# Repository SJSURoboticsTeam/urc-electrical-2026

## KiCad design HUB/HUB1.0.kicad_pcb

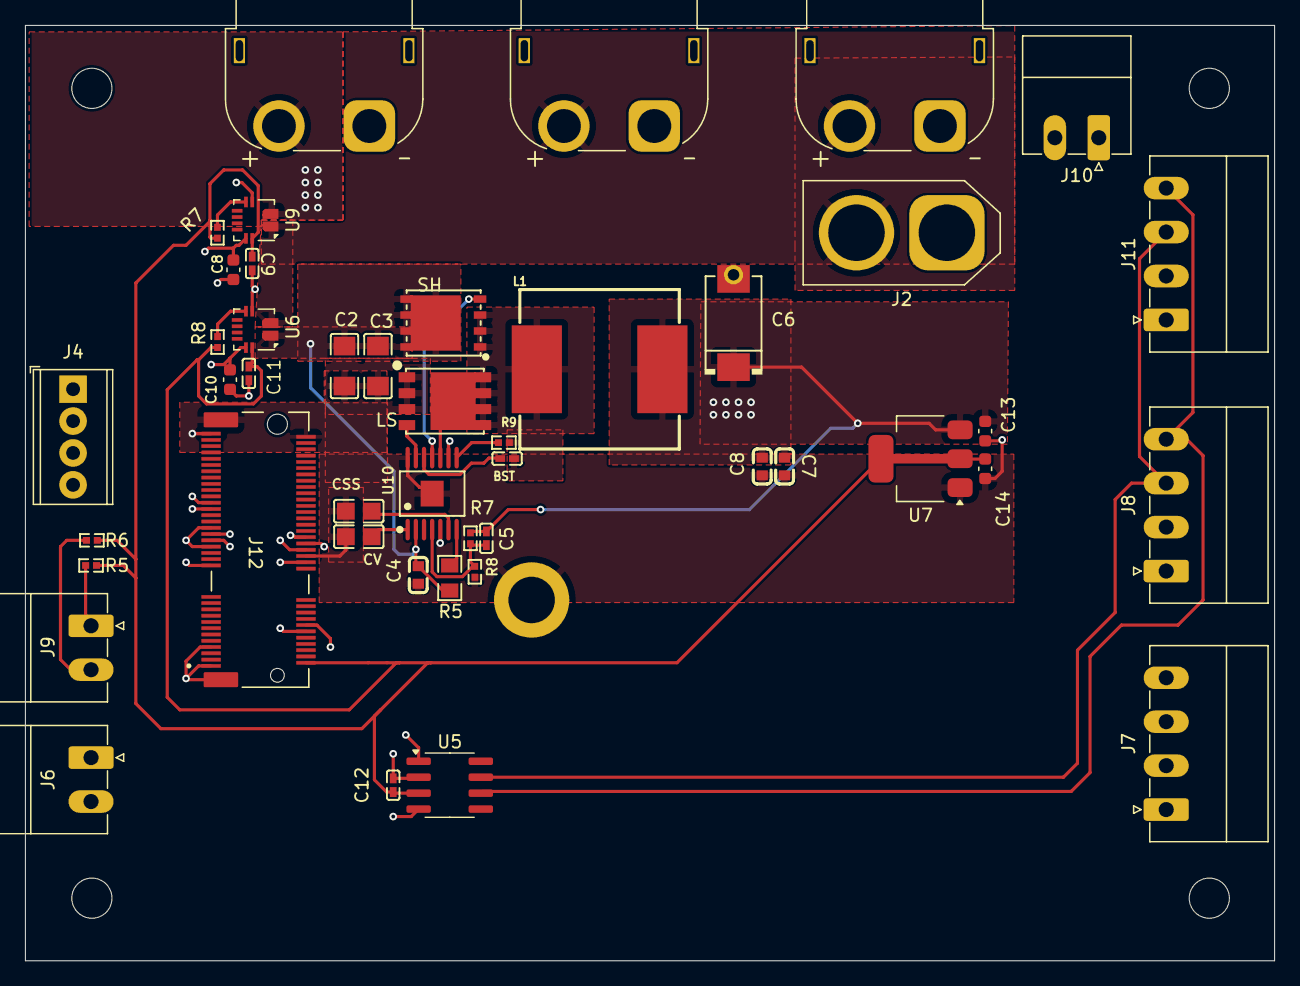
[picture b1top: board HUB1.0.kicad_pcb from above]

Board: 4 copper layers, 99.5 x 74.5 mm, 45 parts (0 on the bottom side), 29 nets.

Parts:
BST: C0402
C2, C3: C1206
C4, C7, C8#2: C0603
C5: C0402
C6: CAP-SMD_L7.3-W4.3-R-RD
C8, C10: 18pF; C_0603_1608Metric
C9, C11, C12: 100nF; C0402
C13, C14: 10µF; C_0603_1608Metric
CSS: C0805
CV: C0805
HS: DFN-8_L5.9-W5.2-P1.27-LS6.2-BL
J1, J3, J5: XT60-PW-M; AMASS_XT60PW-F_1x02_P7.20mm_Horizontal
J2: XT60-PW-M; AMASS_XT60-F_1x02_P7.20mm_Vertical
J4: 2.54mm LCD; TerminalBlock_Phoenix_MPT-0,5-4-2.54_1x04_P2.54mm_Horizontal
J6, J10: Phoenix (5V,GND); PhoenixContact_MC_1,5_2-G-3.5_1x02_P3.50mm_Horizontal
J7: Phoenix (GPIO, 5V, GND); PhoenixContact_MC_1,5_4-G-3.5_1x04_P3.50mm_Horizontal
J8, J11: Phoenix (+,-,CANH/L); PhoenixContact_MC_1,5_4-G-3.5_1x04_P3.50mm_Horizontal
J9: Phoenix (SDA/L); PhoenixContact_MC_1,5_2-G-3.5_1x02_P3.50mm_Horizontal
J12: MicroMod; micromod
L1: IND-SMD_L12.7-W12.7
LS: POWERVDFN-8_L6.0-W5.0-P1.27-BL
R5: R0805
R5#2, R6, R7, R8: 10K; R0402
R7#2, R8#2, R9: R0402
U5: SN65HVD232; SOIC-8_3.9x4.9mm_P1.27mm
U6, U9: ACS711xEXLT-31AB; Allegro_QFN-12-10-1EP_3x3mm_P0.5mm
U7: AMS1117-3.3; SOT-223-3_TabPin2
U10: HTSSOP-14_L5.0-W4.4-P0.65-LS6.4-BL-EP

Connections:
3.3V: C9.1, C11.1, C12.1, C14.1, J12.2 (VCC), R5#2.1, R6.1, R7.2, R8.2, U5.3 (VCC), U6.10 (VCC), U7.2 (VO), U9.10 (VCC)
5V: C5.1, C6.1, C7.1, C8#2.1, C13.1, J4.4, J6.1, J7.1, J8.1, J10.1, J11.1, L1.2, R7#2.2, U7.3 (VI)
40V: C2.2, C3.2, C4.2, HS.5, HS.6, HS.7, HS.8, HS.9, R5.2, U6.1 (IP+), U10.2
$2N671: BST.1, U10.12
$2N681: R5.1, U10.7
$2N1026: CSS.2, U10.6
$2N1121: CV.2, U10.1
$2N1983: C5.2, R7#2.1, R8#2.2, U10.4
$2N2778: BST.2, HS.1, HS.2, HS.3, L1.1, LS.5, LS.6, LS.7, LS.8, LS.9, R9.2, U10.10
$2N2800: LS.4, U10.13
$2N2931: R9.1, U10.8
ADC1: C8.1, J12.34 (A0), U9.9 (VIOUT)
ADC2: C10.1, J12.38 (A0), U6.9 (VIOUT)
GATE: HS.4, U10.11
GND: C2.1, C3.1, C4.1, C6.2, C7.2, C8.2, C8#2.2, C9.2, C10.2, C11.2, C12.2, C13.2, C14.2, CSS.1, CV.1, J1.1, J2.1, J3.1, J4.3, J5.1, J6.2, J7.2, J8.2, J10.2, J11.2, J12.1 (GND), J12.7 (GND), J12.33 (GND), J12.36 (GND), J12.39 (GND), J12.45 (GND), J12.74 (GND), J12.75 (GND), J12.S1 (GND), J12.S2 (GND), J12.S3 (GND), LS.1, LS.2, LS.3, R8#2.1, U5.2 (GND), U6.3 (GND), U7.1 (GND), U9.3 (GND), U10.5, U10.9, U10.14, U10.15
unnamed: J1.2, J2.2, J5.2, U6.2 (IP-), U9.1 (IP+)
unnamed: J3.2, U9.2 (IP-)
unnamed: J8.3, J11.3, U5.7 (CANH)
unnamed: J8.4, J11.4, U5.6 (CANL)
unnamed: J7.4, J12.40 (G0/BUS0)
unnamed: J7.3, J12.42 (G1/BUS1)
unnamed: R8.1, U6.4 (~FAULT)
unnamed: R7.1, U9.4 (~FAULT)
RX: J12.41 (CAN_RX), U5.4 (R)
SCL: J9.2, J12.14 (I2C_SCL), R6.2
SCL2: J4.1, J12.53 (I2C1_SCL)
SDA: J9.1, J12.12 (I2C_SDA), R5#2.2
SDA2: J4.2, J12.51 (I2C1_SDA)
TX: J12.43 (CAN_TX), U5.1 (D)

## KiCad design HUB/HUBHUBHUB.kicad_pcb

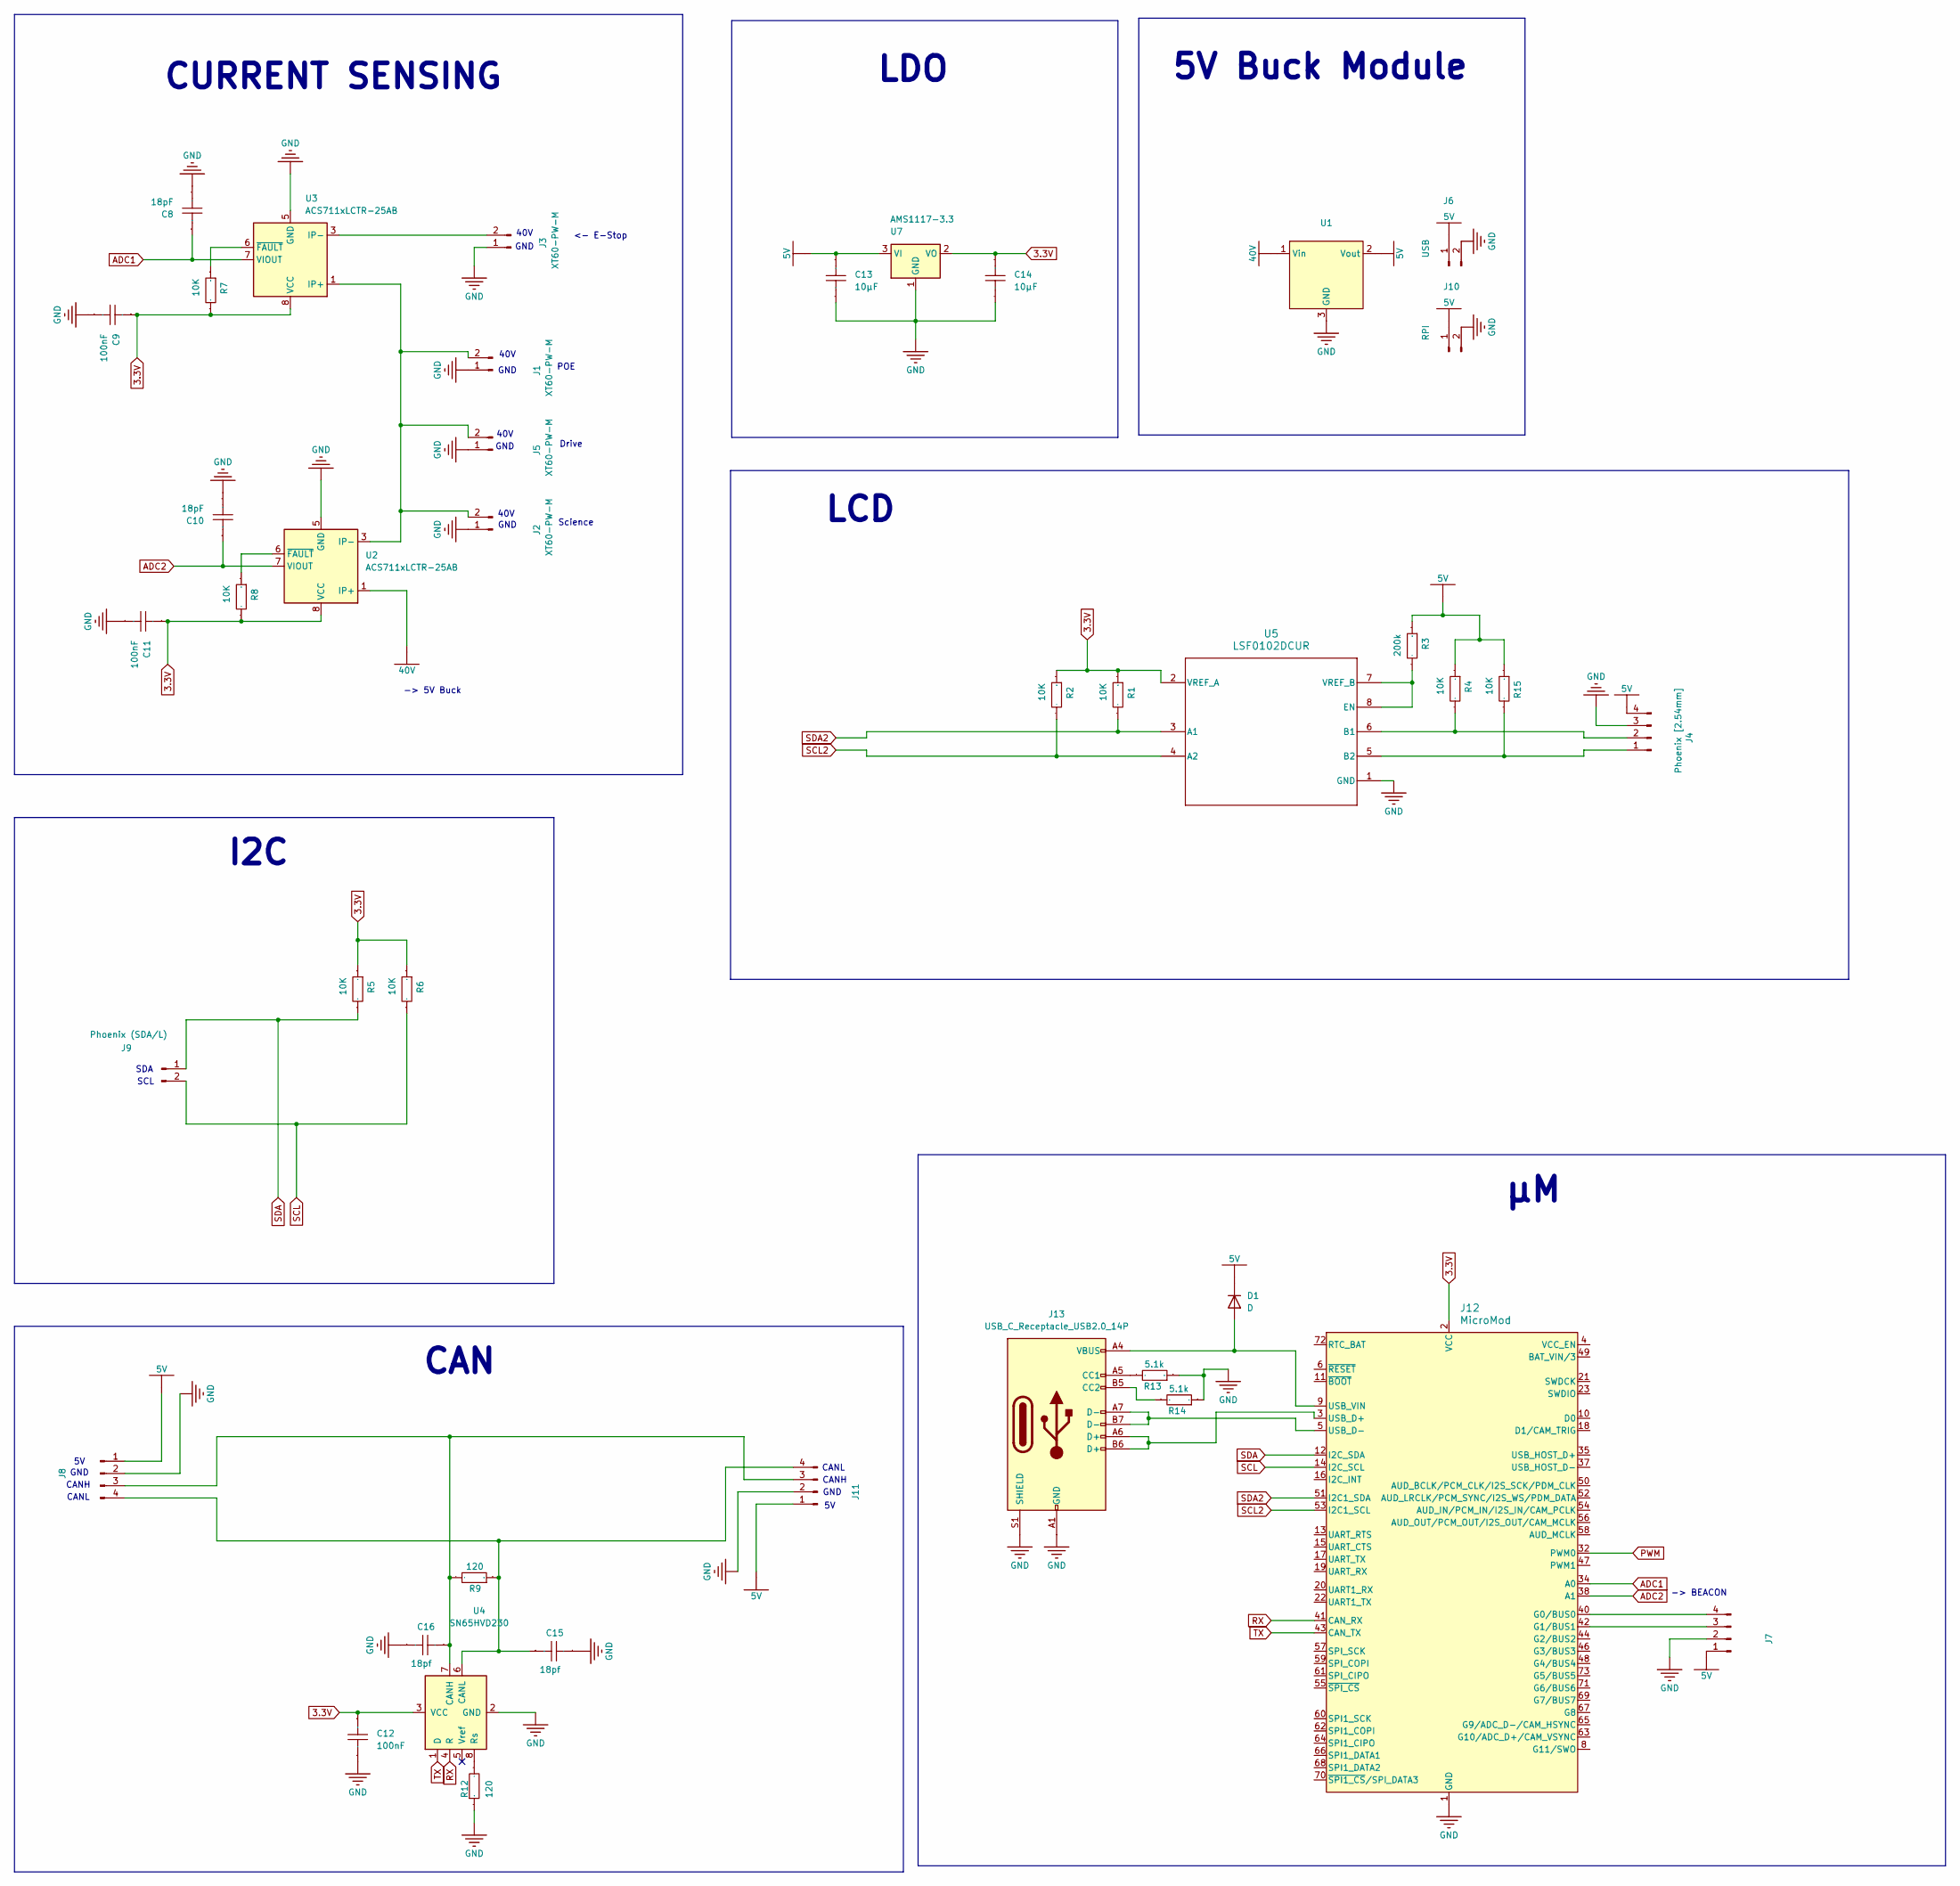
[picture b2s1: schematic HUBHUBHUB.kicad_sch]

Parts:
C8, C10: 18pF; C_0603_1608Metric
C9, C11, C12: 100nF; C0402
C13, C14: 10µF; C_0603_1608Metric
C15, C16: 18pf; C_0603_1608Metric
D1: D; Vishay_SMPA
J1, J2, J3, J5: XT60-PW-M; AMASS_XT60PW-M_1x02_P7.20mm_Horizontal
J4, J7, J8, J11: Phoenix [2.54mm]; TerminalBlock_Phoenix_MPT-0,5-4-2.54_1x04_P2.54mm_Horizontal
J6: USB; TerminalBlock_Phoenix_MPT-0,5-2-2.54_1x02_P2.54mm_Horizontal
J9: Phoenix (SDA/L); TerminalBlock_Phoenix_MPT-0,5-2-2.54_1x02_P2.54mm_Horizontal
J10: RPI; TerminalBlock_Phoenix_MPT-0,5-2-2.54_1x02_P2.54mm_Horizontal
J12: MicroMod; micromod
J13: USB_C_Receptacle_USB2.0_14P; USB_C_Receptacle_HRO_TYPE-C-31-M-12
R1, R2, R4, R5, R6, R7, R8, R15: 10K; R_0603_1608Metric
R3: 200k; R_0603_1608Metric
R9, R12: 120; R_0603_1608Metric
R13, R14: 5.1k; R_0603_1608Metric
U1: 5VBuckModule
U2, U3: ACS711xLCTR-25AB; SOIC-8_3.9x4.9mm_P1.27mm
U4: SN65HVD230; SOIC-8_3.9x4.9mm_P1.27mm
U5: LSF0102DCUR
U7: AMS1117-3.3; SOT-223-3_TabPin2

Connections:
3.3V: C9.1, C11.1, C12.1, C14.1, J12.2 (VCC), J12.74 (VCC), R1.1, R2.1, R5.1, R6.1, R7.2, R8.2, U2.8 (VCC), U3.8 (VCC), U4.3 (VCC), U5.2 (VREF_A), U7.2 (VO)
5V: C13.1, D1.1 (K), J4.4, J6.1, J7.1, J8.1, J10.1, J11.1, R3.1, R4.1, R15.1, U1.2 (Vout), U7.3 (VI)
40V: U1.1 (Vin), U2.1 (IP+), U2.2 (IP+)
ADC1: C8.1, J12.34 (A0), U3.7 (VIOUT)
ADC2: C10.1, J12.38 (A1), U2.7 (VIOUT)
GND: C8.2, C9.2, C10.2, C11.2, C12.2, C13.2, C14.2, C15.2, C16.1, J1.1, J2.1, J3.1, J4.3, J5.1, J6.2, J7.2, J8.2, J10.2, J11.2, J12.1 (GND), J12.7 (GND), J12.33 (GND), J12.36 (GND), J12.39 (GND), J12.45 (GND), J12.75 (GND), J12.S1 (GND), J12.S2 (GND), J12.S3 (GND), J13.A1 (GND), J13.A12 (GND), J13.B1 (GND), J13.B12 (GND), J13.S1 (SHIELD), R12.1, R13.1, R14.1, U1.3 (GND), U2.5 (GND), U3.5 (GND), U4.2 (GND), U5.1 (GND), U7.1 (GND)
unnamed: D1.2 (A), J12.9 (USB_VIN), J13.A4 (VBUS), J13.A9 (VBUS), J13.B4 (VBUS), J13.B9 (VBUS)
unnamed: J1.2, J2.2, J5.2, U2.3 (IP-), U2.4 (IP-), U3.1 (IP+), U3.2 (IP+)
unnamed: J3.2, U3.3 (IP-), U3.4 (IP-)
unnamed: J4.1, R15.2, U5.5 (B2)
unnamed: J4.2, R4.2, U5.6 (B1)
unnamed: C16.2, J8.3, J11.3, R9.2, U4.7 (CANH)
unnamed: C15.1, J8.4, J11.4, R9.1, U4.6 (CANL)
unnamed: J7.4, J12.40 (G0/BUS0)
unnamed: J7.3, J12.42 (G1/BUS1)
unnamed: J12.3 (USB_D+), J13.A6 (D+), J13.B6 (D+)
unnamed: J12.5 (USB_D-), J13.A7 (D-), J13.B7 (D-)
unnamed: J13.A5 (CC1), R13.2
unnamed: J13.B5 (CC2), R14.2
unnamed: R8.1, U2.6 (~FAULT)
unnamed: R7.1, U3.6 (~FAULT)
unnamed: R12.2, U4.8 (Rs)
unnamed: R3.2, U5.7 (VREF_B), U5.8 (EN)
PWM: J12.32 (PWM0)
RX: J12.41 (CAN_RX), U4.4 (R)
SCL: J9.2, J12.14 (I2C_SCL), R6.2
SCL2: J12.53 (I2C1_SCL), R2.2, U5.4 (A2)
SDA: J9.1, J12.12 (I2C_SDA), R5.2
SDA2: J12.51 (I2C1_SDA), R1.2, U5.3 (A1)
TX: J12.43 (CAN_TX), U4.1 (D)

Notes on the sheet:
GND
40V
I2C
CANH
CURRENT SENSING
CAN
SCL
POE
CANL
Drive
Science
<- E-Stop
-> 5V Buck
SDA
LDO
-> BEACON
5V Buck Module
LCD

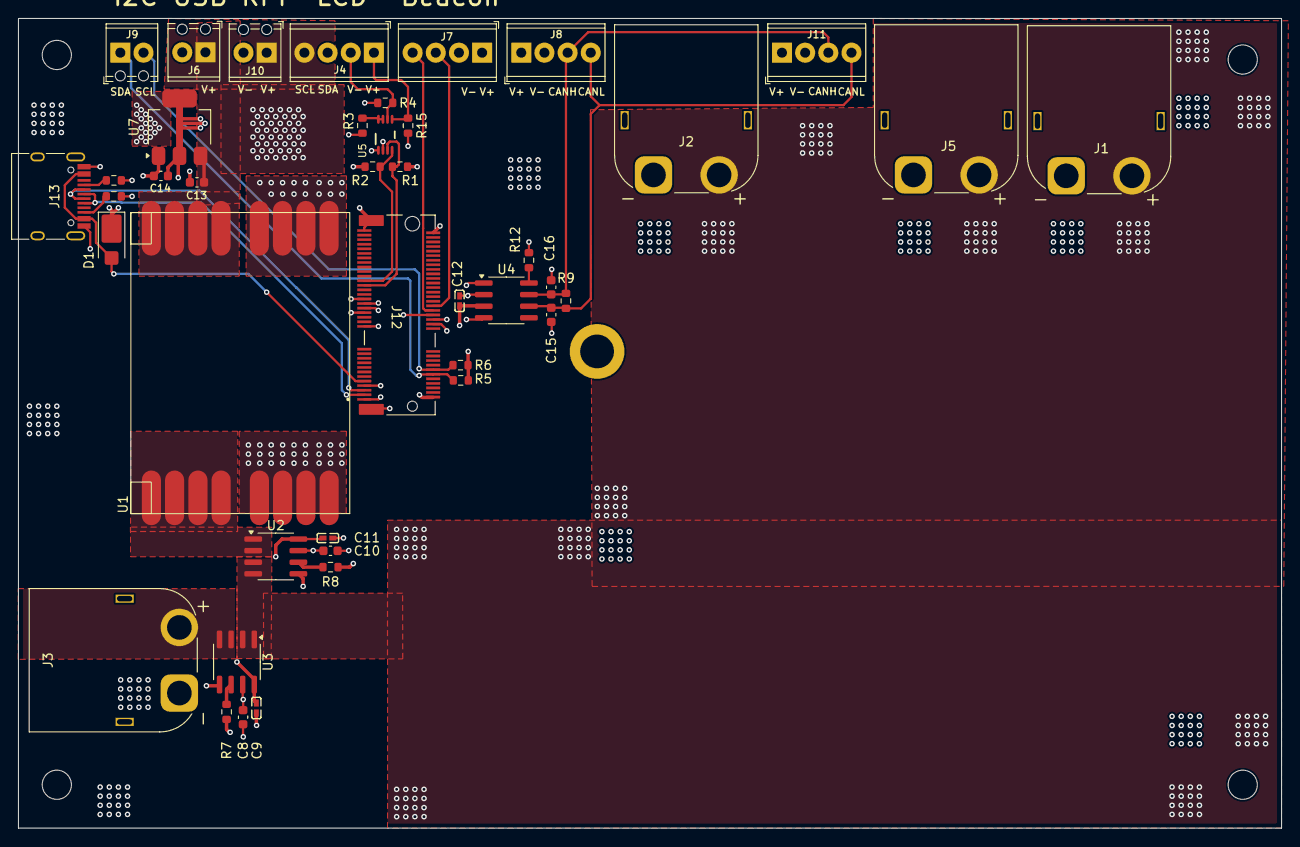
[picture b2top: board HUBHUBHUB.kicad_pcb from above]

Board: 4 copper layers, 138.5 x 88.8 mm, 42 parts (0 on the bottom side), 29 nets.
